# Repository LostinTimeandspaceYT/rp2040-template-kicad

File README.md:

# RP2040 Template KiCAD Project

This project is bsed off the RP2040 Hardware Design document provided by Raspberry Pi and Pimironi's schematics.

This project was created using KiCAD 8.0.0

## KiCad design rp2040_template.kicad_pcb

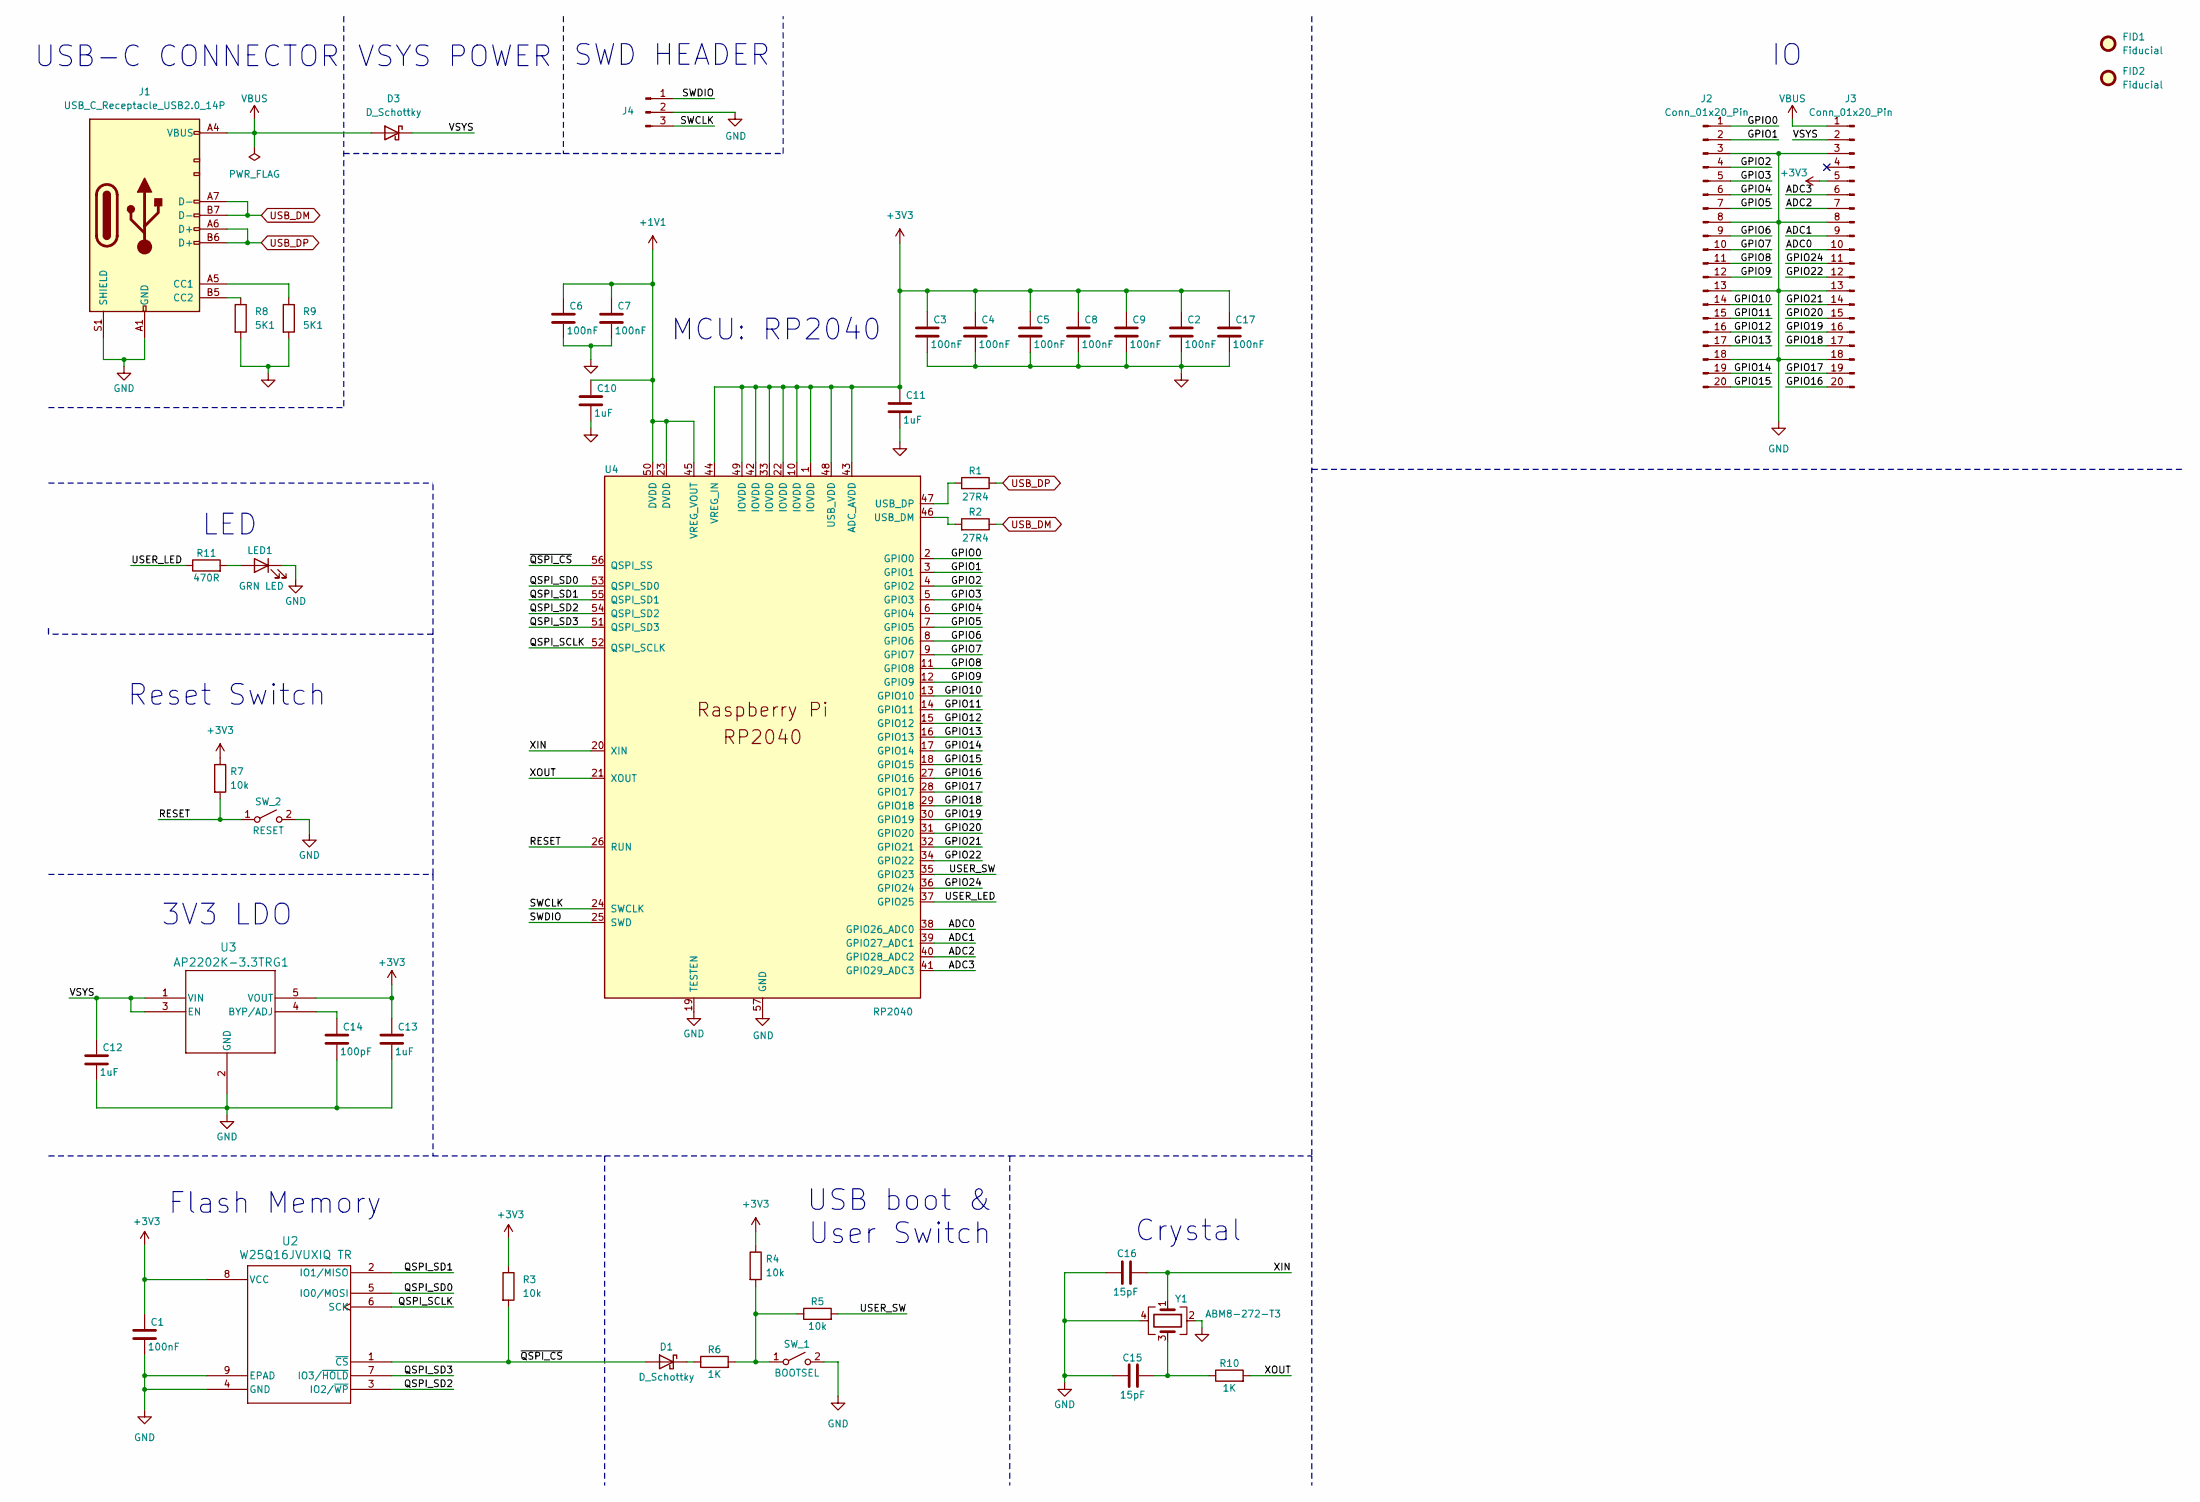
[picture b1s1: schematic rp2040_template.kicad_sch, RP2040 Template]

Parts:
C1, C3, C4, C5, C6, C7, C8, C9, C17: 100nF; C_01005_0402Metric
C2: 100nF; C_0201_0603Metric
C10, C11, C12, C13: 1uF; C_01005_0402Metric
C14: 100pF; C_01005_0402Metric
C15, C16: 15pF; C_01005_0402Metric
D1: D_Schottky; D_01005_0402Metric
D3: D_Schottky; Nexperia_CFP3_SOD-123W
FID1, FID2: Fiducial; Fiducial_0.5mm_Mask1mm
J1: USB_C_Receptacle_USB2.0_14P; USB_C_Receptacle_HRO_TYPE-C-31-M-12
J2, J3: Conn_01x20_Pin; castellated_tht_1x20
J4: Conn_01x03_Pin; castellated_tht_1x3
LED1: GRN LED; LED_0402_1005Metric_Pad0.77x0.64mm_HandSolder
R1, R2: 27R4; R_0201_0603Metric
R3, R4, R5, R7: 10k; R_0201_0603Metric
R6, R10: 1K; R_0201_0603Metric
R8, R9: 5K1; R_0201_0603Metric
R11: 470R; R_0201_0603Metric
SW_1: BOOTSEL; SW_SPST_PTS810
SW_2: RESET; SW_SPST_PTS810
U2: W25Q16JVUXIQ TR; Winbond_USON-8-1EP_3x2mm_P0.5mm_EP0.2x1.6mm
U3: AP2202K-3.3TRG1; SOT-23-5_AP2202_DIO
U4: RP2040; QFN-56-1EP_7x7mm_P0.4mm_EP3.2x3.2mm
Y1: ABM8-272-T3; Crystal_SMD_2520-4Pin_2.5x2.0mm

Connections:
+1V1: C6.1, C7.1, C10.1, U4.23 (DVDD), U4.45 (VREG_VOUT), U4.50 (DVDD)
+3V3: C1.1, C2.1, C3.1, C4.1, C5.1, C8.1, C9.1, C11.1, C13.1, C17.1, J3.5, R3.1, R4.1, R7.1, U2.8 (VCC), U3.5 (VOUT), U4.1 (IOVDD), U4.10 (IOVDD), U4.22 (IOVDD), U4.33 (IOVDD), U4.42 (IOVDD), U4.43 (ADC_AVDD), U4.44 (VREG_IN), U4.48 (USB_VDD), U4.49 (IOVDD); also elsewhere on the board
/ADC0: J3.10, U4.38 (GPIO26_ADC0)
/ADC1: J3.9, U4.39 (GPIO27_ADC1)
/ADC2: J3.7, U4.40 (GPIO28_ADC2)
/ADC3: J3.6, U4.41 (GPIO29_ADC3)
/GPIO0: J2.1, U4.2 (GPIO0)
/GPIO1: J2.2, U4.3 (GPIO1)
/GPIO2: J2.4, U4.4 (GPIO2)
/GPIO3: J2.5, U4.5 (GPIO3)
/GPIO4: J2.6, U4.6 (GPIO4)
/GPIO5: J2.7, U4.7 (GPIO5)
/GPIO6: J2.9, U4.8 (GPIO6)
/GPIO7: J2.10, U4.9 (GPIO7)
/GPIO8: J2.11, U4.11 (GPIO8)
/GPIO9: J2.12, U4.12 (GPIO9)
/GPIO10: J2.14, U4.13 (GPIO10)
/GPIO11: J2.15, U4.14 (GPIO11)
/GPIO12: J2.16, U4.15 (GPIO12)
/GPIO13: J2.17, U4.16 (GPIO13)
/GPIO14: J2.19, U4.17 (GPIO14)
/GPIO15: J2.20, U4.18 (GPIO15)
/GPIO16: J3.20, U4.27 (GPIO16)
/GPIO17: J3.19, U4.28 (GPIO17)
/GPIO18: J3.17, U4.29 (GPIO18)
/GPIO19: J3.16, U4.30 (GPIO19)
/GPIO20: J3.15, U4.31 (GPIO20)
/GPIO21: J3.14, U4.32 (GPIO21)
/GPIO22: J3.12, U4.34 (GPIO22)
/GPIO24: J3.11, U4.36 (GPIO24)
/QSPI_SCLK: U2.6 (SCK), U4.52 (QSPI_SCLK)
/QSPI_SD0: U2.5 (IO0/MOSI), U4.53 (QSPI_SD0)
/QSPI_SD1: U2.2 (IO1/MISO), U4.55 (QSPI_SD1)
/QSPI_SD2: U2.3 (IO2/~WP), U4.54 (QSPI_SD2)
/QSPI_SD3: U2.7 (IO3/~HOLD), U4.51 (QSPI_SD3)
/RESET: R7.2, SW_2.1 (A), U4.26 (RUN)
/SWCLK: J4.3, U4.24 (SWCLK)
/SWDIO: J4.1, U4.25 (SWD)
/USER_LED: R11.1, U4.37 (GPIO25)
/USER_SW: R5.2, U4.35 (GPIO23)
/VSYS: C12.1, D3.1 (K), J3.2, U3.1 (VIN), U3.3 (EN)
/XIN: C16.2, U4.20 (XIN), Y1.1
/XOUT: R10.2, U4.21 (XOUT)
/~QSPI_CS: D1.2 (A), R3.2, U2.1 (~CS), U4.56 (QSPI_SS)
GND: C1.2, C2.2, C3.2, C4.2, C5.2, C6.2, C7.2, C8.2, C9.2, C10.2, C11.2, C12.2, C13.2, C14.2, C15.1, C16.1, C17.2, J1.A1 (GND), J1.A12 (GND), J1.B1 (GND), J1.B12 (GND), J1.S1 (SHIELD), J2.3, J2.8, J2.13, J2.18, J3.3, J3.8, J3.13, J3.18, J4.2, LED1.1 (K), R8.2, R9.2, SW_1.2 (B), SW_2.2 (B), U2.4 (GND), U2.9 (EPAD), U3.2 (GND), U4.19 (TESTEN), U4.57 (GND), Y1.2, Y1.4; also elsewhere on the board
unnamed: C15.2, R10.1, Y1.3
unnamed: D1.1 (K), R6.1
unnamed: J1.A5 (CC1), R9.1
unnamed: J1.B5 (CC2), R8.1
unnamed: LED1.2 (A), R11.2
unnamed: R4.2, R5.1, R6.2, SW_1.1 (A)
unnamed: C14.1, U3.4 (BYP/ADJ)
unnamed: R2.2, U4.46 (USB_DM)
unnamed: R1.2, U4.47 (USB_DP)
USB_DM: J1.A7 (D-), J1.B7 (D-), R2.1
USB_DP: J1.A6 (D+), J1.B6 (D+), R1.1
VBUS: D3.2 (A), J1.A4 (VBUS), J1.A9 (VBUS), J1.B4 (VBUS), J1.B9 (VBUS), J3.1

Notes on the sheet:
USB boot & User Switch
Reset Switch
USB-C CONNECTOR
Flash Memory
VSYS POWER
MCU: RP2040
3V3 LDO
LED
Crystal
SWD HEADER

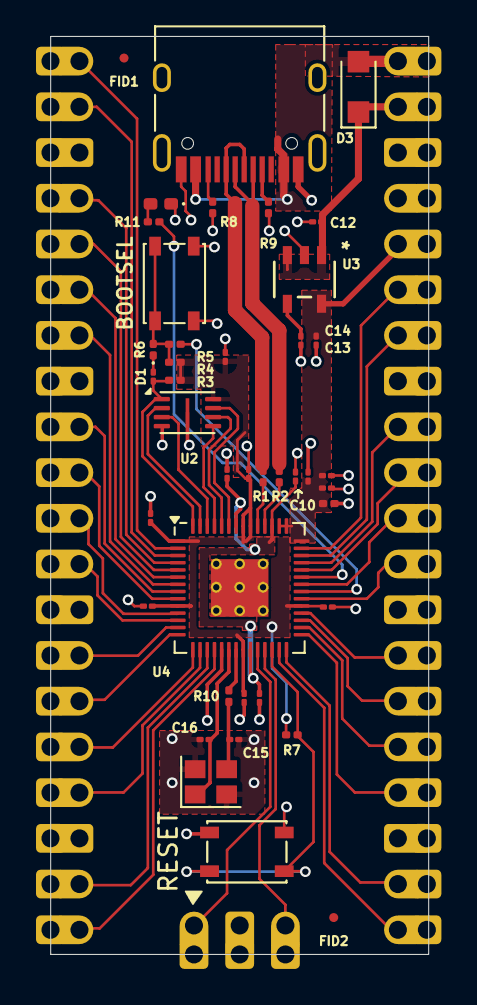
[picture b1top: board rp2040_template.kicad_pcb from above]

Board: 2 copper layers, 21.0 x 51.0 mm, 44 parts (1 on the bottom side), 57 nets.

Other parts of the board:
C2#2: 100nF; C_01005_0402Metric

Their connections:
+3V3: C2#2.1; also elsewhere on the board
GND: C2#2.2; also elsewhere on the board

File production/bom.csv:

Designator,Footprint,Quantity,Value,LCSC Part #
"_9, _8, _7, _6, _5, _4, _3, _2, ",,9,,
"C1, C17, C2, C3, C4, C5, C6, C7, C8, C9",01005,10,100nF,
"C10, C11, C12, C13",01005,4,1uF,
C14,01005,1,100pF,
"C15, C16",01005,2,15pF,
C2_2,0201,1,100nF,
D1,01005,1,D_Schottky,
D3,Nexperia_CFP3_SOD-123W,1,D_Schottky,
J1,USB_C_Receptacle_HRO_TYPE-C-31-M-12,1,USB_C_Receptacle_USB2.0_14P,
"J2, J3",castellated_tht_1x20,2,Conn_01x20_Pin,
J4,castellated_tht_1x3,1,Conn_01x03_Pin,
LED1,0402,1,GRN LED,
"R1, R2",0201,2,27R4,
"R10, R6",0201,2,1K,
R11,0201,1,470R,
"R3, R4, R5, R7",0201,4,10k,
"R8, R9",0201,2,5K1,
SW_1,SW_SPST_PTS810,1,BOOTSEL,
SW_2,SW_SPST_PTS810,1,RESET,
U2,Winbond_USON-8-1EP_3x2mm_P0.5mm_EP0.2x1.6mm,1,W25Q16JVUXIQ TR,
U3,SOT-23-5_AP2202_DIO,1,AP2202K-3.3TRG1,
U4,QFN-56-1EP_7x7mm_P0.4mm_EP3.2x3.2mm,1,RP2040,
Y1,Crystal_SMD_2520-4Pin_2.5x2.0mm,1,ABM8-272-T3,

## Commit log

2024-04-06 initial commit.
2024-04-06 Added PDF.
2024-09-06 Added Footprints to components.
    Signed-off-by Nathan <natelostintimeandspace@gmail.com>
2024-11-04 Added castellated edges to PCB. began work on layout.
2024-11-04 added .lck files to gitignore.
2024-11-04 added autosave to gitignore.
2024-11-06 Routed USB data, Oscillator, and began QSPI layout.
2024-11-11 Finished Rev A!
